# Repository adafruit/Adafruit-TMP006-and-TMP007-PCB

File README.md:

# Adafruit TMP006 and TMP007 PCBs
&nbsp; <br />
Click to purchase from the Adafruit Shop:
- [Contact-less Infrared Thermopile Sensor Breakout - TMP006](https://www.adafruit.com/product/1296)
- [Contact-less Infrared Thermopile Sensor Breakout - TMP007 (DISCONTINUED)](https://www.adafruit.com/product/2023)

Unlike all the other temperature sensors we have, this breakout has a really cool IR sensor from TI that can measure the temperature of an object without touching it! Simply point the sensor towards what you want to measure and it will detect the temperature by absorbing IR waves emitted. The embedded thermopile sensor generates a very very small voltage depending on how much IR there is, and using some math, that micro voltage can be used to calculate the temperature. It also takes the measurement over an area so it can be handy for determining the average temperature of something.

These are the Eagle CAD files for the Adafruit TMP006/TMP007 sensor breakout (same layout, different silkscreen):

  ----> https://www.adafruit.com/products/1296

  ----> https://www.adafruit.com/products/2023 (DISCONTINUED)

### License

Adafruit invests time and resources providing this open source design, please support Adafruit and open-source hardware by [purchasing products from Adafruit](https://www.adafruit.com)!

All text above must be included in any redistribution

Designed by Limor Fried/Ladyada for Adafruit Industries.
Creative Commons Attribution/Share-Alike, all text above must be included in any redistribution. 
See license.txt for additional information.

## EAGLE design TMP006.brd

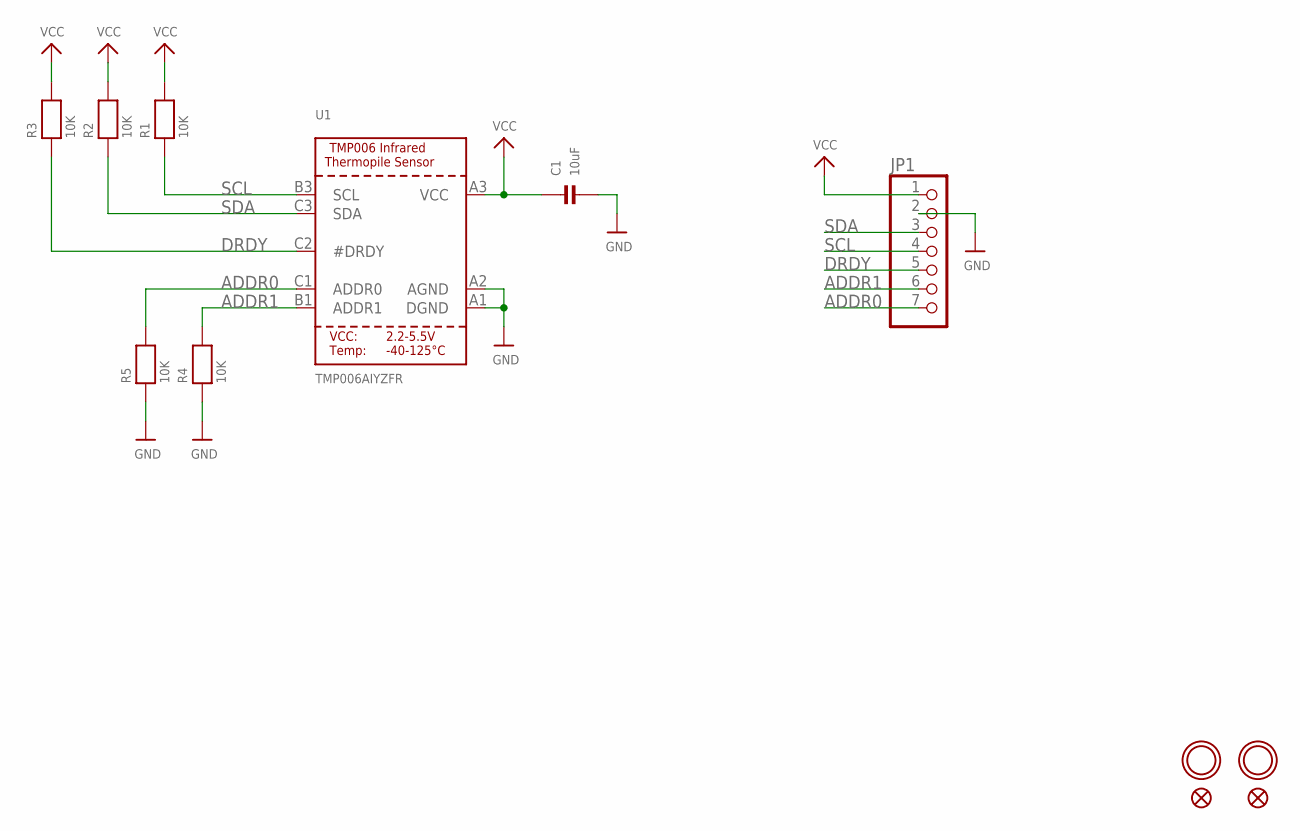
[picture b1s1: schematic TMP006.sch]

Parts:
C1: 10uF; 0805
FID1, FID2: FIDUCIAL""; FIDUCIAL_1MM
JP1: HEADER-1X7THICKER; 1X07_ROUND_76
R1, R2, R3, R4, R5: 10K; 0805
U1: TMP006AIYZFR; WCSP-8
U$6, U$7: MOUNTINGHOLE2.5; MOUNTINGHOLE_2.5_PLATED

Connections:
ADDR0: JP1.7, R5.2, U1.C1 (ADDR0)
ADDR1: JP1.6, R4.2, U1.B1 (ADDR1)
DRDY: JP1.5, R3.1, U1.C2 (#DRDY)
GND: C1.2, JP1.2, R4.1, R5.1, U1.A1 (DGND), U1.A2 (AGND)
SCL: JP1.4, R1.1, U1.B3 (SCL)
SDA: JP1.3, R2.1, U1.C3 (SDA)
VCC: C1.1, JP1.1, R1.2, R2.2, R3.2, U1.A3 (VCC)

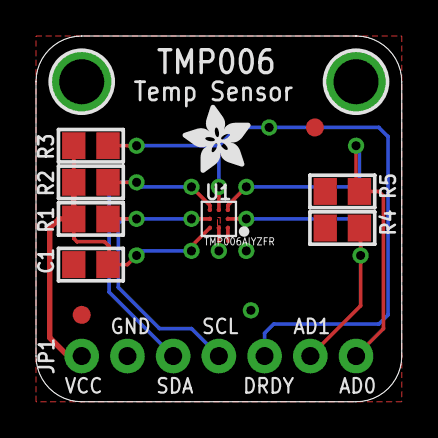
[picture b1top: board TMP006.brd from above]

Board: 2 copper layers, 20.3 x 20.3 mm, 13 parts (0 on the bottom side), 7 nets.

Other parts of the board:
U$9: ADAFRUIT_3.5MM

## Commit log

2014-09-16 init

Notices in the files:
parts and their libraries:
microbuilder: This work is placed in the public domain, and may be freely used for commercial and non-commercial work with the following conditions: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
